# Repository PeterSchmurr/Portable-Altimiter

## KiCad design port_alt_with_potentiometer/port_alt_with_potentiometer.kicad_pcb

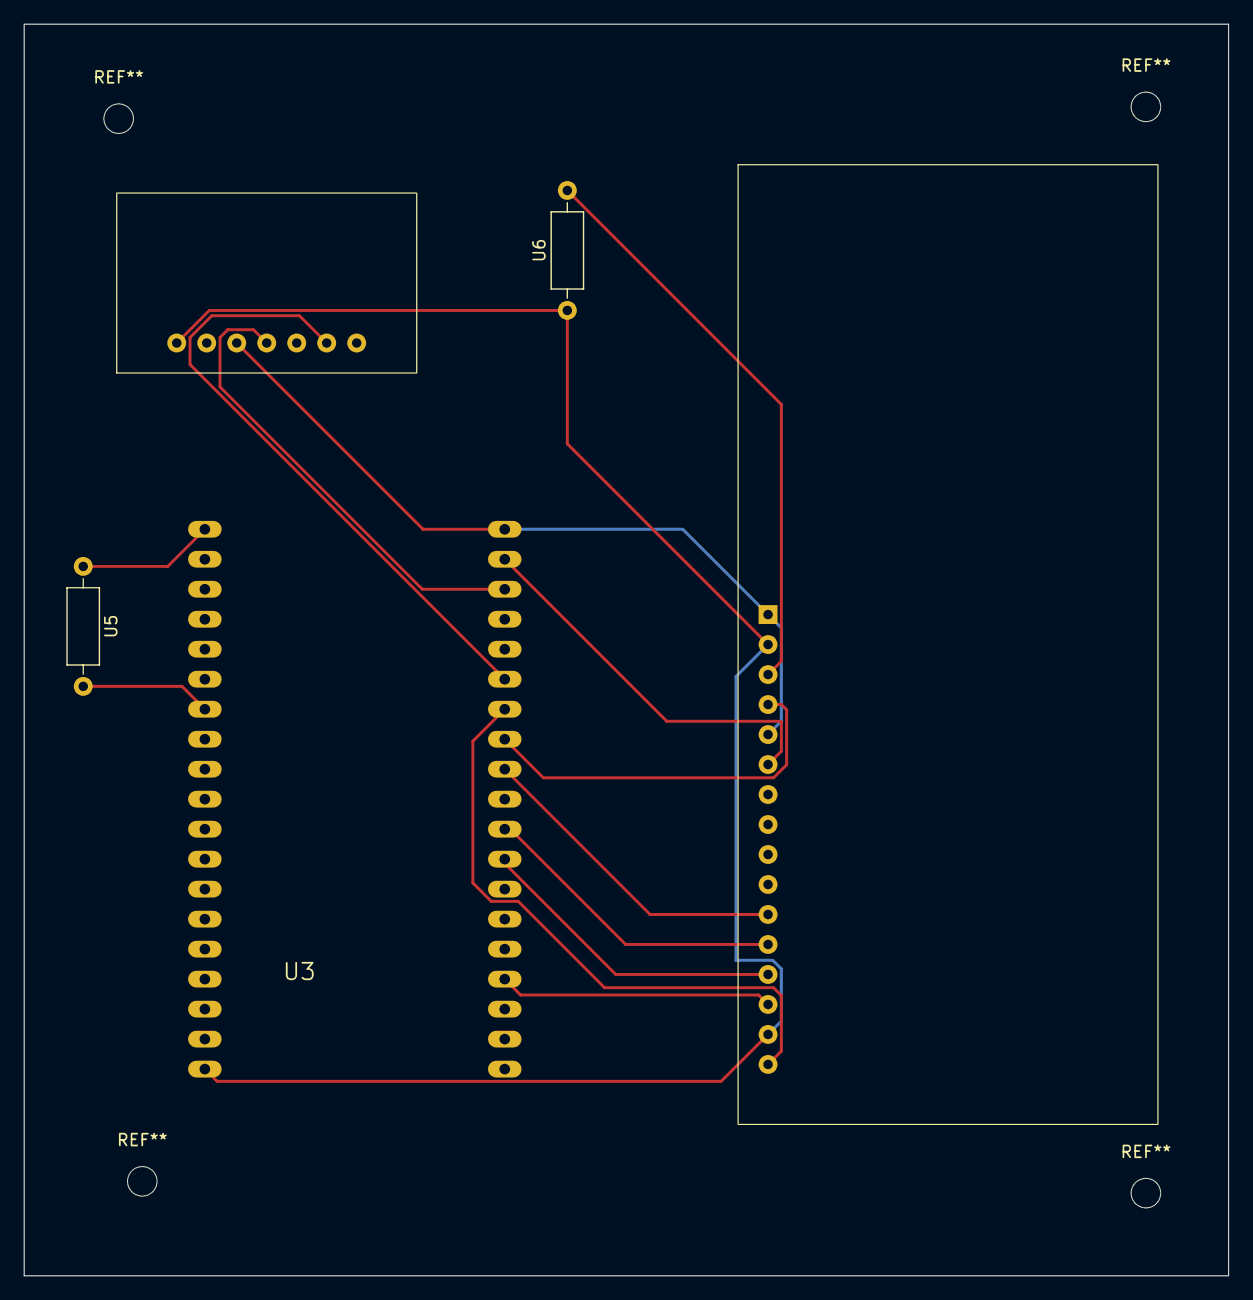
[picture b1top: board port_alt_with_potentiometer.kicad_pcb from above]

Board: 2 copper layers, 102.0 x 106.0 mm, 5 parts (0 on the bottom side), 14 nets.

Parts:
U1: LCD16X02
U2: 2652; BMP280
U3: NODEMCU32S
U5, U6: R_Axial_DIN0207_L6.3mm_D2.5mm_P10.16mm_Horizontal

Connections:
/5V: U1.2 (vdd), U1.15 (A), U2.1 (VIN), U3.VIN, U6.1 (R1)
/GND: U1.1 (vss), U1.5 (RW), U2.3 (GND), U3.GND@2
/V0: U1.3 (v0), U6.2 (R2)
unnamed: U1.11 (D4), U3.GPIO18
unnamed: U1.12 (D5), U3.GPIO17
unnamed: U1.13 (D6), U3.GPIO16
unnamed: U1.14 (D7), U3.GPIO15
unnamed: U1.6 (E), U3.GPIO23
unnamed: U1.16 (K), U3.GND@3
unnamed: U1.4 (RS), U3.GPIO19
unnamed: U2.4 (SCK), U3.GPIO22
unnamed: U2.6 (SDI), U3.GPIO21
unnamed: U3.3V3 (3.3V), U5.1 (SPST1)
unnamed: U3.GPIO32, U5.2 (SPST2)

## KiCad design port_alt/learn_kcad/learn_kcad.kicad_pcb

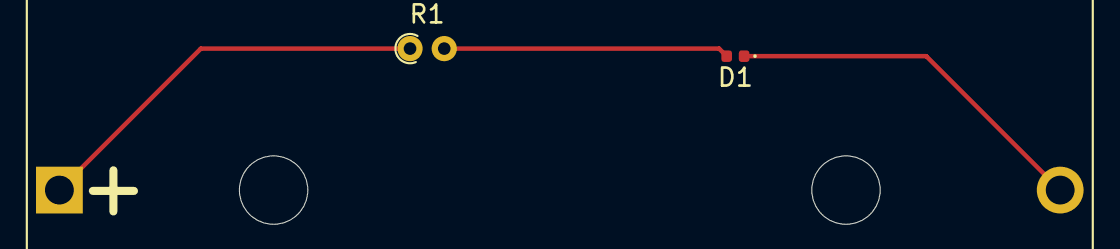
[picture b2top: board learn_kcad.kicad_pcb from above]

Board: 2 copper layers, 3 parts (0 on the bottom side), 3 nets.

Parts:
BT1: 3v; BatteryHolder_Bulgin_BX0036_1xC
D1: red; LED_0402_1005Metric
R1: 1k; R_Axial_DIN0204_L3.6mm_D1.6mm_P1.90mm_Vertical

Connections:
/led: D1.2 (A), R1.2
GND: BT1.2 (-), D1.1 (K)
VCC: BT1.1 (+), R1.1

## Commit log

2023-04-10 add zero pushbutton capability
2023-04-11 add constant for zero button....add initialization pins for LCD
2023-04-11 add variables and pin assignments
2023-04-21 update program to reset to zero when button is pushed
2023-09-28 incorporated rate functions
2023-10-09 configured rate calculation and display
2023-10-10 change rate output to float
2023-10-10 change git repository location
2023-10-12 change loop delay from 500 to 2500 ms
2023-10-19 change documentation to reflect global scope for variables
2023-10-24 add v2.3
2023-10-25 add global variables for central control
2023-11-22 add version 2.4 with 5 point derivative and reduced sensor precision
